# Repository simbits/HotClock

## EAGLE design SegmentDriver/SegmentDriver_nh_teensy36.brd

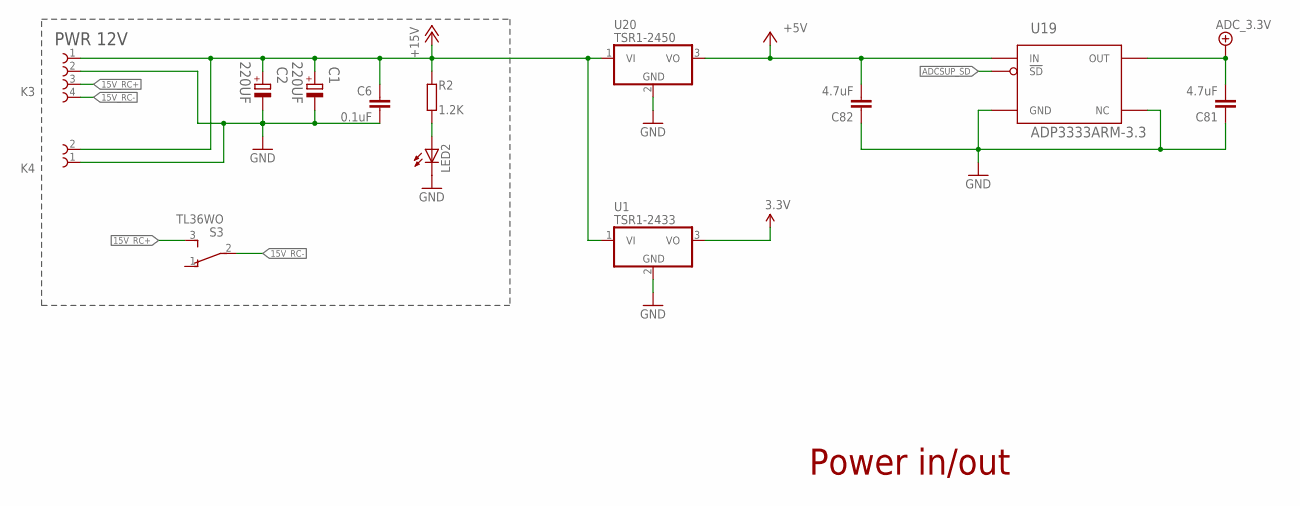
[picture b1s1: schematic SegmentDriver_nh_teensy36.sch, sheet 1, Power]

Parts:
C1, C2: 220UF; CAPAE830X1050N
C6: 0.1uF; C0603K
C81: 4.7uF; C0603K
C82: 4.7uF; C0805K
K3: 691322310004
K4: 691322310002
LED2: LEDCHIPLED_0603; CHIPLED_0603
R2: 1.2K; R0603
S3: TL36WO; TL3XWO
U1: TSR1-2433; TO220V_TR1; FARNELL_OC 1696320
U19: ADP3333ARM-3.3; MSOP-8
U20: TSR1-2450; TO220V_TR1; FARNELL_OC 1696320

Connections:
3.3V: U1.3 (VO); also elsewhere on the board
15V_RC+: K3.3, S3.3 (S)
15V_RC-: K3.4, S3.2
!ADCSUP_SD: U19.7 (!SD!); also elsewhere on the board
+5V: C82.2, U19.2 (IN), U20.3 (VO); also elsewhere on the board
+15V: C1.1, C2.1, C6.2, K3.1, K4.2, R2.2, U1.1 (VI), U20.1 (VI); also elsewhere on the board
ADC_3.3V: C81.2, U19.1 (OUT); also elsewhere on the board
GND: C1.2, C2.2, C6.1, C81.1, C82.1, K3.2, K4.1, LED2.C, U1.2 (GND), U19.3 (GND), U19.4 (NC), U19.5 (NC), U19.6 (NC), U19.8 (NC), U20.2 (GND); also elsewhere on the board
unnamed: LED2.A, R2.1

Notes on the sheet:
PWR 12V
Power in/out

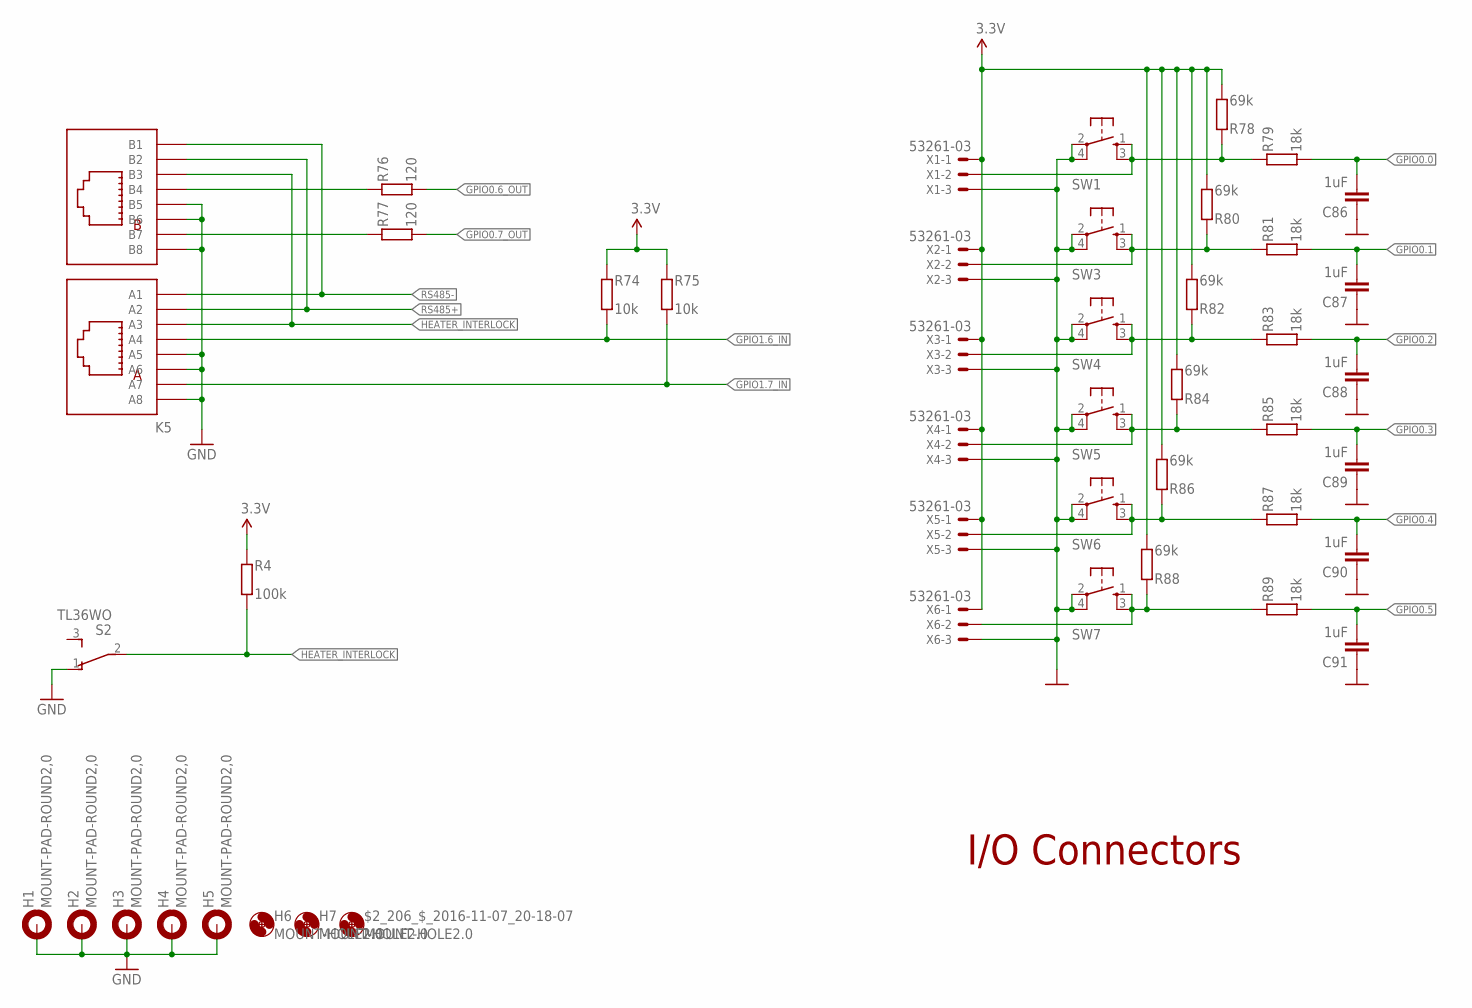
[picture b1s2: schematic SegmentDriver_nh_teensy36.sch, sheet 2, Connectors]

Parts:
$2_206_$_2016-11-07_20-18-07: MOUNT-HOLE2.0; 2,0
C86, C87, C88, C89, C90, C91: 1uF; C0603K
H1, H2, H3, H4, H5: MOUNT-PAD-ROUND2,0; 2,0-PAD
H6, H7: MOUNT-HOLE2.0; 2,0
K5: 615016149521
R4: 100k; R0603
R74, R75: 10k; R0603
R76, R77: 120; R0603
R78, R80, R82, R84, R86, R88: 69k; R0603
R79, R81, R83, R85, R87, R89: 18k; R0603
S2: TL36WO; TL3XWO
SW1, SW3, SW4, SW5, SW6, SW7: 434153017835_FIXED; 434153017835
X1, X2, X3, X4, X5, X6: 53261-03

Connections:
3.3V: R4.2, R74.2, R75.2, R78.1, R80.1, R82.1, R84.1, R86.1, R88.1, X1.1, X2.1, X3.1, X4.1, X5.1, X6.1; also elsewhere on the board
GND: C86.1, C87.1, C88.1, C89.1, C90.1, C91.1, H1.B2,2, H2.B2,2, H3.B2,2, H4.B2,2, H5.B2,2, K5.A5, K5.A6, K5.A8, K5.B5, K5.B6, K5.B8, S2.1 (O), SW1.2, SW1.4, SW3.2, SW3.4, SW4.2, SW4.4, SW5.2, SW5.4, SW6.2, SW6.4, SW7.2, SW7.4, X1.3, X2.3, X3.3, X4.3, X5.3, X6.3; also elsewhere on the board
GPIO0.0: C86.2, R79.1; also elsewhere on the board
GPIO0.1: C87.2, R81.1; also elsewhere on the board
GPIO0.2: C88.2, R83.1; also elsewhere on the board
GPIO0.3: C89.2, R85.1; also elsewhere on the board
GPIO0.4: C90.2, R87.1; also elsewhere on the board
GPIO0.5: C91.2, R89.1; also elsewhere on the board
GPIO0.6_OUT: R76.1; also elsewhere on the board
GPIO0.7_OUT: R77.1; also elsewhere on the board
GPIO1.6_IN: K5.A4, R74.1; also elsewhere on the board
GPIO1.7_IN: K5.A7, R75.1; also elsewhere on the board
GPIO6_OUT: K5.B4, R76.2
GPIO7_OUT: K5.B7, R77.2
HEATER_INTERLOCK: K5.A3, R4.1, S2.2; also elsewhere on the board
unnamed: R78.2, R79.2, SW1.1, SW1.3, X1.2
unnamed: R80.2, R81.2, SW3.1, SW3.3, X2.2
unnamed: R82.2, R83.2, SW4.1, SW4.3, X3.2
unnamed: R84.2, R85.2, SW5.1, SW5.3, X4.2
unnamed: R86.2, R87.2, SW6.1, SW6.3, X5.2
unnamed: R88.2, R89.2, SW7.1, SW7.3, X6.2
RS485+: K5.A2, K5.B2; also elsewhere on the board
RS485-: K5.A1, K5.B1; also elsewhere on the board

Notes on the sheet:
I/O Connectors

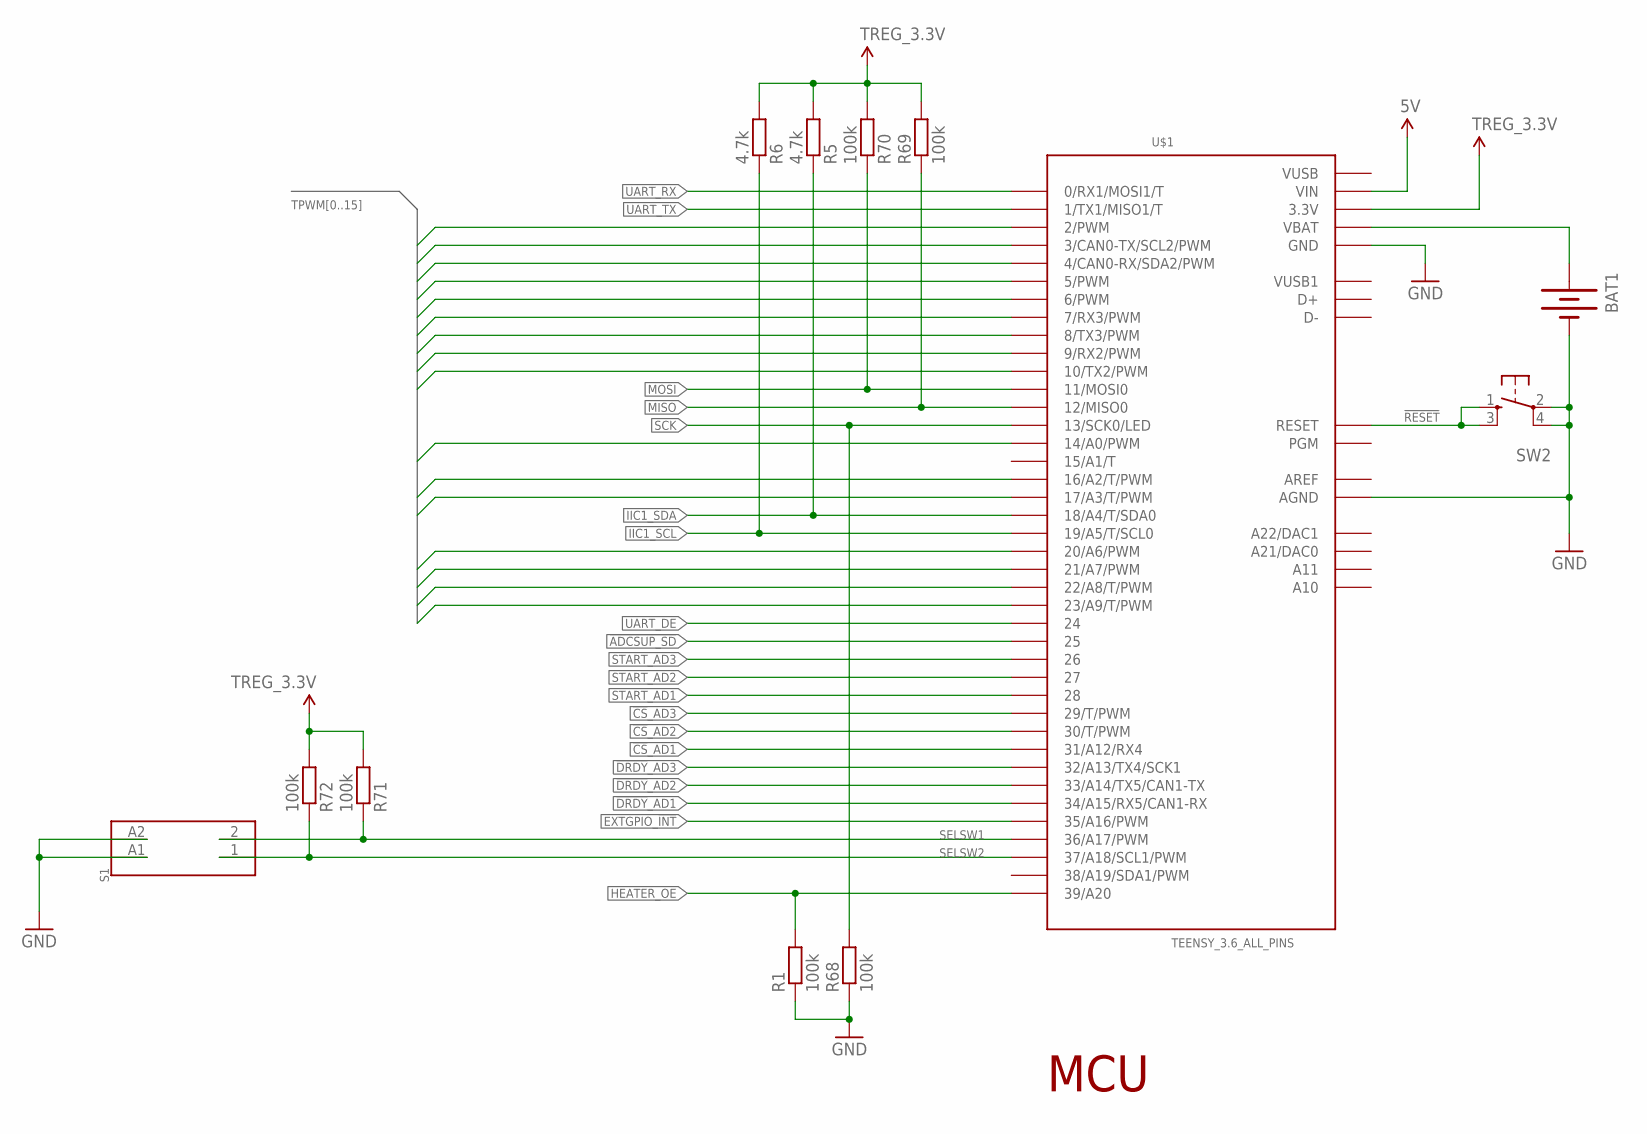
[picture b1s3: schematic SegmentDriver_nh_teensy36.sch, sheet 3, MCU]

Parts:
BAT1: BATTERY-79528211; 79528211; DIGIKEY BK-912-CT-ND
R1, R68, R69, R70, R71, R72: 100k; R0603
R5, R6: 4.7k; R0603
S1: 418127270902
SW2: 434153017835_FIXED; 434153017835
U$1: TEENSY_3.6_ALL_PINS

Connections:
5V: U$1.VIN
!ADCSUP_SD: U$1.25; also elsewhere on the board
!CS!_AD1: U$1.31/A12 (31/A12/RX4); also elsewhere on the board
!CS!_AD2: U$1.30 (30/T/PWM); also elsewhere on the board
!CS!_AD3: U$1.29 (29/T/PWM); also elsewhere on the board
!DRDY!_AD1: U$1.34/A15 (34/A15/RX5/CAN1-RX); also elsewhere on the board
!DRDY!_AD2: U$1.33/A14 (33/A14/TX5/CAN1-TX); also elsewhere on the board
!DRDY!_AD3: U$1.32/A13 (32/A13/TX4/SCK1); also elsewhere on the board
!RESET: SW2.1, SW2.3, U$1.RESET
AREF: U$1.AREF
EXTGPIO_!INT: U$1.35/A16 (35/A16/PWM); also elsewhere on the board
GND: BAT1.-, R1.1, R68.1, S1.A1, S1.A2, SW2.2, SW2.4, U$1.AGND, U$1.GND, U$1.GND1 (GND), U$1.GND3 (GND), U$1.GND4 (GND), U$1.GND6 (GND); also elsewhere on the board
HEATER_OE: R1.2, U$1.39/A20; also elsewhere on the board
IIC1_SCL: R6.1, U$1.19/A5 (19/A5/T/SCL0); also elsewhere on the board
IIC1_SDA: R5.1, U$1.18/A4 (18/A4/T/SDA0); also elsewhere on the board
MISO: R69.1, U$1.12 (12/MISO0); also elsewhere on the board
MOSI: R70.1, U$1.11 (11/MOSI0); also elsewhere on the board
unnamed: BAT1.+, U$1.VBAT
SCK: R68.2, U$1.13 (13/SCK0/LED); also elsewhere on the board
SELSW1: R71.1, S1.2, U$1.36/A17 (36/A17/PWM)
SELSW2: R72.1, S1.1, U$1.37/A18 (37/A18/SCL1/PWM)
START_AD1: U$1.28; also elsewhere on the board
START_AD2: U$1.27; also elsewhere on the board
START_AD3: U$1.26; also elsewhere on the board
TPWM0: U$1.2 (2/PWM)
TPWM1: U$1.3 (3/CAN0-TX/SCL2/PWM)
TPWM2: U$1.4 (4/CAN0-RX/SDA2/PWM)
TPWM3: U$1.5 (5/PWM)
TPWM4: U$1.6 (6/PWM)
TPWM5: U$1.7 (7/RX3/PWM)
TPWM6: U$1.8 (8/TX3/PWM)
TPWM7: U$1.9 (9/RX2/PWM)
TPWM8: U$1.10 (10/TX2/PWM)
TPWM9: U$1.14/A0 (14/A0/PWM)
TPWM10: U$1.16/A2 (16/A2/T/PWM)
TPWM11: U$1.17/A3 (17/A3/T/PWM)
TPWM12: U$1.20/A6 (20/A6/PWM)
TPWM13: U$1.21/A7 (21/A7/PWM)
TPWM14: U$1.22/A8 (22/A8/T/PWM)
TPWM15: U$1.23/A9 (23/A9/T/PWM)
TREG_3.3V: R5.2, R6.2, R69.2, R70.2, R71.2, R72.2, U$1.3.3V, U$1.3.3V3 (3.3V), U$1.3.3V4 (3.3V); also elsewhere on the board
UART_DE: U$1.24; also elsewhere on the board
UART_RX: U$1.0 (0/RX1/MOSI1/T); also elsewhere on the board
UART_TX: U$1.1 (1/TX1/MISO1/T); also elsewhere on the board
VUSB: U$1.VUSB
VUSB1: U$1.VUSB1

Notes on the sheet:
MCU

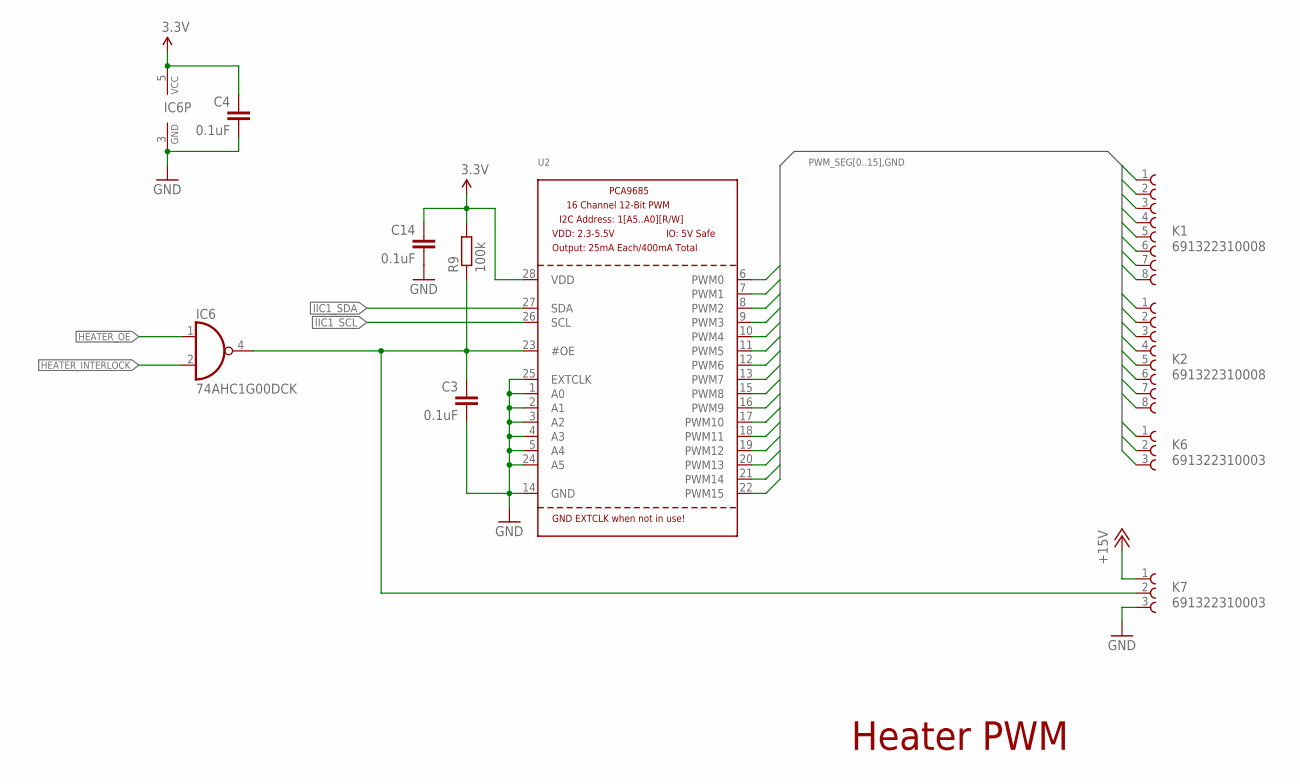
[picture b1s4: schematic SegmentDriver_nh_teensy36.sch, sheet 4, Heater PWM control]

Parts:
C3, C4, C14: 0.1uF; C0603K
IC6: 74AHC1G00DCK; SC70-5
K1, K2: 691322310008
K6, K7: 691322310003
R9: 100k; R0603
U2: PCA9685; TSSOP28

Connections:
3.3V: C4.1, C14.1, IC6.5 (VCC), R9.2, U2.28 (VDD); also elsewhere on the board
+15V: K7.1; also elsewhere on the board
GND: C3.2, C4.2, C14.2, IC6.3 (GND), K1.1, K2.1, K6.1, K7.3, U2.1 (A0), U2.2 (A1), U2.3 (A2), U2.4 (A3), U2.5 (A4), U2.14 (GND), U2.24 (A5), U2.25 (EXTCLK); also elsewhere on the board
HEATER_INTERLOCK: IC6.2 (I1); also elsewhere on the board
HEATER_OE: IC6.1 (I0); also elsewhere on the board
HEATER_PWR_EN: C3.1, IC6.4 (O), K7.2, R9.1, U2.23 (#OE)
IIC1_SCL: U2.26 (SCL); also elsewhere on the board
IIC1_SDA: U2.27 (SDA); also elsewhere on the board
PWM_SEG0: K1.2, U2.6 (PWM0)
PWM_SEG1: K1.3, U2.7 (PWM1)
PWM_SEG2: K1.4, U2.8 (PWM2)
PWM_SEG3: K1.5, U2.9 (PWM3)
PWM_SEG4: K1.6, U2.10 (PWM4)
PWM_SEG5: K1.7, U2.11 (PWM5)
PWM_SEG6: K1.8, U2.12 (PWM6)
PWM_SEG7: K2.2, U2.13 (PWM7)
PWM_SEG8: K2.3, U2.15 (PWM8)
PWM_SEG9: K2.4, U2.16 (PWM9)
PWM_SEG10: K2.5, U2.17 (PWM10)
PWM_SEG11: K2.6, U2.18 (PWM11)
PWM_SEG12: K2.7, U2.19 (PWM12)
PWM_SEG13: K2.8, U2.20 (PWM13)
PWM_SEG14: K6.2, U2.21 (PWM14)
PWM_SEG15: K6.3, U2.22 (PWM15)

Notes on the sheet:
Heater PWM

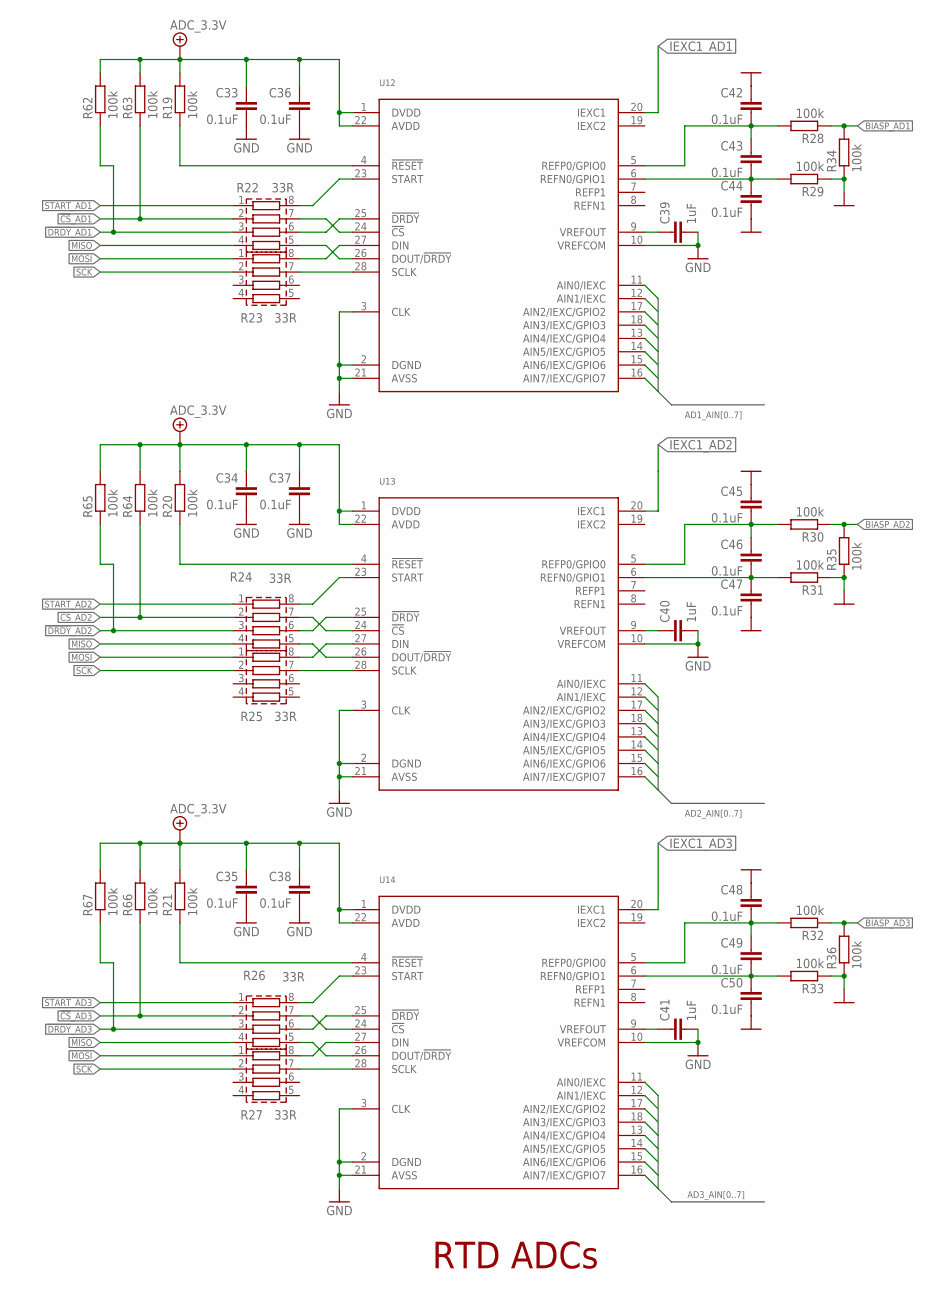
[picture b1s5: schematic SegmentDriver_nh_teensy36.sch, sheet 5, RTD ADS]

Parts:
C33, C34, C35, C36, C37, C38, C42, C43, C44, C45, C46, C47, C48, C49, C50: 0.1uF; C0603K
C39, C40, C41: 1uF; C0603K
R19, R20, R21, R28, R29, R30, R31, R32, R33, R34, R35, R36, R62, R63, R64, R65, R66, R67: 100k; R0603
R22, R23, R24, R25, R26, R27: 33R; RESCAV80P320X160X70-8N; MPN EXBV8V470JV
U12, U13, U14: ADS1X48IPW; TSSOP28

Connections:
9_AD1: C39.1, U12.9 (VREFOUT)
9_AD2: C40.1, U13.9 (VREFOUT)
9_AD3: C41.1, U14.9 (VREFOUT)
23_AD1: R22.8, U12.23 (START)
23_AD2: R24.8, U13.23 (START)
23_AD3: R26.8, U14.23 (START)
24_AD1: R22.7, U12.24 (!CS!)
24_AD2: R24.7, U13.24 (!CS!)
24_AD3: R26.7, U14.24 (!CS!)
25_AD1: R22.6, U12.25 (!DRDY!)
25_AD2: R24.6, U13.25 (!DRDY!)
25_AD3: R26.6, U14.25 (!DRDY!)
26_AD1: R22.5, U12.26 (DOUT/!DRDY!)
26_AD2: R24.5, U13.26 (DOUT/!DRDY!)
26_AD3: R26.5, U14.26 (DOUT/!DRDY!)
27_AD1: R23.8, U12.27 (DIN)
27_AD2: R25.8, U13.27 (DIN)
27_AD3: R27.8, U14.27 (DIN)
28_AD1: R23.7, U12.28 (SCLK)
28_AD2: R25.7, U13.28 (SCLK)
28_AD3: R27.7, U14.28 (SCLK)
!CS!_AD1: R22.2, R63.1; also elsewhere on the board
!CS!_AD2: R24.2, R64.1; also elsewhere on the board
!CS!_AD3: R26.2, R66.1; also elsewhere on the board
!DRDY!_AD1: R22.3, R62.1; also elsewhere on the board
!DRDY!_AD2: R24.3, R65.1; also elsewhere on the board
!DRDY!_AD3: R26.3, R67.1; also elsewhere on the board
!RESET!_AD1: R19.1, U12.4 (!RESET!)
!RESET!_AD2: R20.1, U13.4 (!RESET!)
!RESET!_AD3: R21.1, U14.4 (!RESET!)
AD1_AIN0: U12.11 (AIN0/IEXC); also elsewhere on the board
AD1_AIN1: U12.12 (AIN1/IEXC); also elsewhere on the board
AD1_AIN2: U12.17 (AIN2/IEXC/GPIO2); also elsewhere on the board
AD1_AIN3: U12.18 (AIN3/IEXC/GPIO3); also elsewhere on the board
AD1_AIN4: U12.13 (AIN4/IEXC/GPIO4); also elsewhere on the board
AD1_AIN5: U12.14 (AIN5/IEXC/GPIO5); also elsewhere on the board
AD1_AIN6: U12.15 (AIN6/IEXC/GPIO6); also elsewhere on the board
AD1_AIN7: U12.16 (AIN7/IEXC/GPIO7); also elsewhere on the board
AD2_AIN0: U13.11 (AIN0/IEXC); also elsewhere on the board
AD2_AIN1: U13.12 (AIN1/IEXC); also elsewhere on the board
AD2_AIN2: U13.17 (AIN2/IEXC/GPIO2); also elsewhere on the board
AD2_AIN3: U13.18 (AIN3/IEXC/GPIO3); also elsewhere on the board
AD2_AIN4: U13.13 (AIN4/IEXC/GPIO4); also elsewhere on the board
AD2_AIN5: U13.14 (AIN5/IEXC/GPIO5); also elsewhere on the board
AD2_AIN6: U13.15 (AIN6/IEXC/GPIO6); also elsewhere on the board
AD2_AIN7: U13.16 (AIN7/IEXC/GPIO7); also elsewhere on the board
AD3_AIN0: U14.11 (AIN0/IEXC); also elsewhere on the board
AD3_AIN1: U14.12 (AIN1/IEXC); also elsewhere on the board
AD3_AIN2: U14.17 (AIN2/IEXC/GPIO2); also elsewhere on the board
AD3_AIN3: U14.18 (AIN3/IEXC/GPIO3); also elsewhere on the board
AD3_AIN4: U14.13 (AIN4/IEXC/GPIO4); also elsewhere on the board
AD3_AIN5: U14.14 (AIN5/IEXC/GPIO5); also elsewhere on the board
AD3_AIN6: U14.15 (AIN6/IEXC/GPIO6); also elsewhere on the board
AD3_AIN7: U14.16 (AIN7/IEXC/GPIO7); also elsewhere on the board
ADC_3.3V: C33.1, C34.1, C35.1, C36.1, C37.1, C38.1, R19.2, R20.2, R21.2, R62.2, R63.2, R64.2, R65.2, R66.2, R67.2, U12.1 (DVDD), U12.22 (AVDD), U13.1 (DVDD), U13.22 (AVDD), U14.1 (DVDD), U14.22 (AVDD); also elsewhere on the board
BIASP_AD1: R28.1, R34.2; also elsewhere on the board
BIASP_AD2: R30.1, R35.2; also elsewhere on the board
BIASP_AD3: R32.1, R36.2; also elsewhere on the board
GND: C33.2, C34.2, C35.2, C36.2, C37.2, C38.2, C39.2, C40.2, C41.2, C42.1, C44.2, C45.1, C47.2, C48.1, C50.2, R29.1, R31.1, R33.1, R34.1, R35.1, R36.1, U12.2 (DGND), U12.3 (CLK), U12.10 (VREFCOM), U12.21 (AVSS), U13.2 (DGND), U13.3 (CLK), U13.10 (VREFCOM), U13.21 (AVSS), U14.2 (DGND), U14.3 (CLK), U14.10 (VREFCOM), U14.21 (AVSS); also elsewhere on the board
IEXC1_AD1: U12.20 (IEXC1); also elsewhere on the board
IEXC1_AD2: U13.20 (IEXC1); also elsewhere on the board
IEXC1_AD3: U14.20 (IEXC1); also elsewhere on the board
MISO: R22.4, R24.4, R26.4; also elsewhere on the board
MOSI: R23.1, R25.1, R27.1; also elsewhere on the board
REFN0_AD1: C43.2, C44.1, R29.2, U12.6 (REFN0/GPIO1)
REFN0_AD2: C46.2, C47.1, R31.2, U13.6 (REFN0/GPIO1)
REFN0_AD3: C49.2, C50.1, R33.2, U14.6 (REFN0/GPIO1)
REFP0_AD1: C42.2, C43.1, R28.2, U12.5 (REFP0/GPIO0)
REFP0_AD2: C45.2, C46.1, R30.2, U13.5 (REFP0/GPIO0)
REFP0_AD3: C48.2, C49.1, R32.2, U14.5 (REFP0/GPIO0)
SCK: R23.2, R25.2, R27.2; also elsewhere on the board
START_AD1: R22.1; also elsewhere on the board
START_AD2: R24.1; also elsewhere on the board
START_AD3: R26.1; also elsewhere on the board

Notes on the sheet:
RTD ADCs

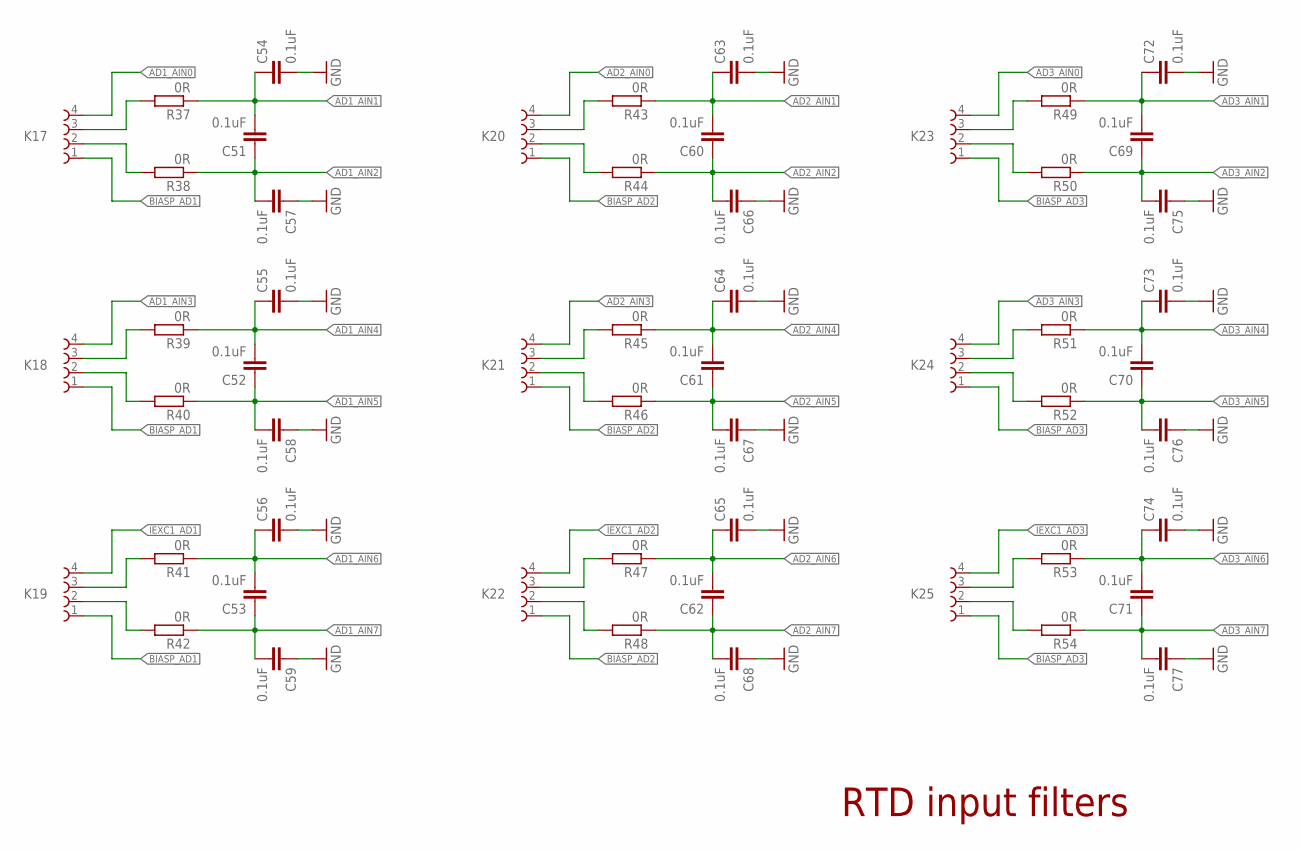
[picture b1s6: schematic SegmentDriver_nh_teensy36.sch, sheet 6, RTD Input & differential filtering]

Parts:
C51, C52, C53, C54, C55, C56, C57, C58, C59, C60, C61, C62, C63, C64, C65, C66, C67, C68, C69, C70, C71, C72, C73, C74, C75, C76, C77: 0.1uF; C0603K
K17, K18, K19, K20, K21, K22, K23, K24, K25: 691210910004
R37, R38, R39, R40, R41, R42, R43, R44, R45, R46, R47, R48, R49, R50, R51, R52, R53, R54: 0R; R0603

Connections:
AD1_AIN0: K17.4; also elsewhere on the board
AD1_AIN1: C51.2, C54.1, R37.1; also elsewhere on the board
AD1_AIN2: C51.1, C57.2, R38.1; also elsewhere on the board
AD1_AIN3: K18.4; also elsewhere on the board
AD1_AIN4: C52.2, C55.1, R39.1; also elsewhere on the board
AD1_AIN5: C52.1, C58.2, R40.1; also elsewhere on the board
AD1_AIN6: C53.2, C56.1, R41.1; also elsewhere on the board
AD1_AIN7: C53.1, C59.2, R42.1; also elsewhere on the board
AD2_AIN0: K20.4; also elsewhere on the board
AD2_AIN1: C60.2, C63.1, R43.1; also elsewhere on the board
AD2_AIN2: C60.1, C66.2, R44.1; also elsewhere on the board
AD2_AIN3: K21.4; also elsewhere on the board
AD2_AIN4: C61.2, C64.1, R45.1; also elsewhere on the board
AD2_AIN5: C61.1, C67.2, R46.1; also elsewhere on the board
AD2_AIN6: C62.2, C65.1, R47.1; also elsewhere on the board
AD2_AIN7: C62.1, C68.2, R48.1; also elsewhere on the board
AD3_AIN0: K23.4; also elsewhere on the board
AD3_AIN1: C69.2, C72.1, R49.1; also elsewhere on the board
AD3_AIN2: C69.1, C75.2, R50.1; also elsewhere on the board
AD3_AIN3: K24.4; also elsewhere on the board
AD3_AIN4: C70.2, C73.1, R51.1; also elsewhere on the board
AD3_AIN5: C70.1, C76.2, R52.1; also elsewhere on the board
AD3_AIN6: C71.2, C74.1, R53.1; also elsewhere on the board
AD3_AIN7: C71.1, C77.2, R54.1; also elsewhere on the board
BIASP_AD1: K17.1, K18.1, K19.1; also elsewhere on the board
BIASP_AD2: K20.1, K21.1, K22.1; also elsewhere on the board
BIASP_AD3: K23.1, K24.1, K25.1; also elsewhere on the board
GND: C54.2, C55.2, C56.2, C57.1, C58.1, C59.1, C63.2, C64.2, C65.2, C66.1, C67.1, C68.1, C72.2, C73.2, C74.2, C75.1, C76.1, C77.1; also elsewhere on the board
IEXC1_AD1: K19.4; also elsewhere on the board
IEXC1_AD2: K22.4; also elsewhere on the board
IEXC1_AD3: K25.4; also elsewhere on the board
unnamed: K18.3, R39.2
unnamed: K18.2, R40.2
unnamed: K17.3, R37.2
unnamed: K17.2, R38.2
unnamed: K19.3, R41.2
unnamed: K19.2, R42.2
unnamed: K20.3, R43.2
unnamed: K20.2, R44.2
unnamed: K21.3, R45.2
unnamed: K21.2, R46.2
unnamed: K22.3, R47.2
unnamed: K22.2, R48.2
unnamed: K23.3, R49.2
unnamed: K23.2, R50.2
unnamed: K24.3, R51.2
unnamed: K24.2, R52.2
unnamed: K25.3, R53.2
unnamed: K25.2, R54.2

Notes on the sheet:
RTD input filters

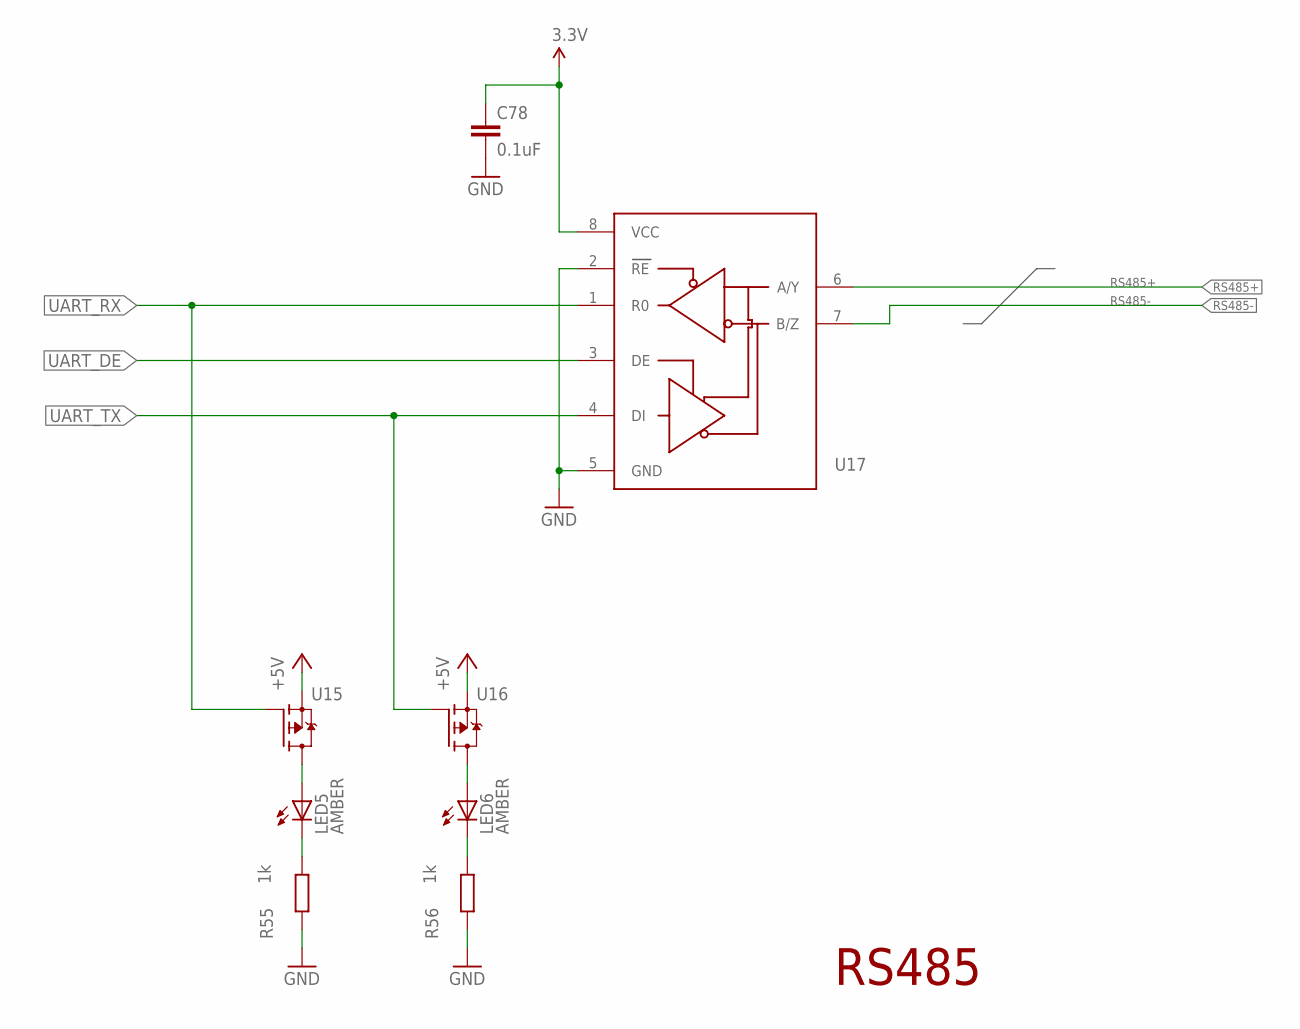
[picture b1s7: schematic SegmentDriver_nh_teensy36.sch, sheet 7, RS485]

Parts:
C78: 0.1uF; C0603K
LED5, LED6: AMBER; CHIPLED_0603
R55, R56: 1k; R0603
U15, U16: DMP2215L-7; SOT95P240X110-3N
U17: ISL83078E; SOIC08

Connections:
3.3V: C78.1, U17.8 (VCC); also elsewhere on the board
+5V: U15.2 (S), U16.2 (S); also elsewhere on the board
GND: C78.2, R55.1, R56.1, U17.2 (RE), U17.5 (GND); also elsewhere on the board
unnamed: LED5.C, R55.2
unnamed: LED6.C, R56.2
unnamed: LED5.A, U15.3 (D)
unnamed: LED6.A, U16.3 (D)
RS485+: U17.6 (A/Y); also elsewhere on the board
RS485-: U17.7 (B/Z); also elsewhere on the board
UART_DE: U17.3 (DE); also elsewhere on the board
UART_RX: U15.1 (G), U17.1 (R0); also elsewhere on the board
UART_TX: U16.1 (G), U17.4 (DI); also elsewhere on the board

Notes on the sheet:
RS485

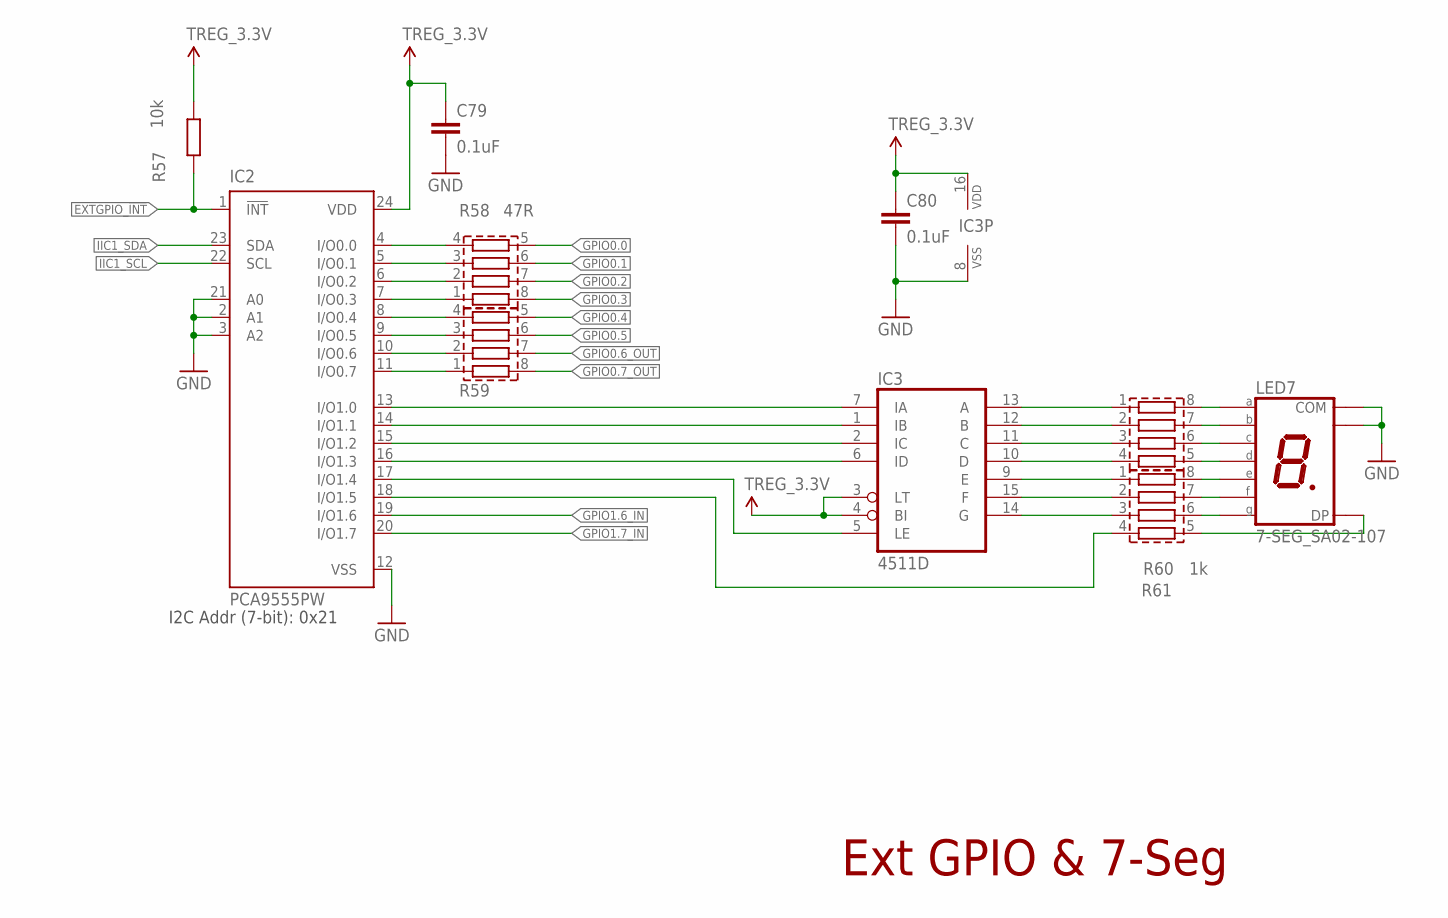
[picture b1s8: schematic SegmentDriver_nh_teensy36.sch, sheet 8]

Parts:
C79, C80: 0.1uF; C0603K
IC2: PCA9555PW; TSSOP24
IC3: 4511D; SO16
LED7: 7-SEG_SA02-107; SA02107
R57: 10k; R0603
R58, R59: 47R; RESCAV80P320X160X70-8N; MPN EXBV8V470JV
R60: 47R; RESCAV80P320X160X70-8N; MPN EXBV8V102JV
R61: 1k; RESCAV80P320X160X70-8N; MPN EXBV8V102JV

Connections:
EXTGPIO_!INT: IC2.1 (!INT), R57.1; also elsewhere on the board
GND: C79.2, C80.2, IC2.2 (A1), IC2.3 (A2), IC2.12 (VSS), IC2.21 (A0), IC3.8 (VSS), LED7.COM@3 (COM), LED7.COM@8 (COM); also elsewhere on the board
GPIO0.0: R58.5; also elsewhere on the board
GPIO0.1: R58.6; also elsewhere on the board
GPIO0.2: R58.7; also elsewhere on the board
GPIO0.3: R58.8; also elsewhere on the board
GPIO0.4: R59.5; also elsewhere on the board
GPIO0.5: R59.6; also elsewhere on the board
GPIO0.6_OUT: R59.7; also elsewhere on the board
GPIO0.7_OUT: R59.8; also elsewhere on the board
GPIO1.6_IN: IC2.19 (I/O1.6); also elsewhere on the board
GPIO1.7_IN: IC2.20 (I/O1.7); also elsewhere on the board
IIC1_SCL: IC2.22 (SCL); also elsewhere on the board
IIC1_SDA: IC2.23 (SDA); also elsewhere on the board
unnamed: IC2.4 (I/O0.0), R58.4
unnamed: IC2.5 (I/O0.1), R58.3
unnamed: IC2.6 (I/O0.2), R58.2
unnamed: IC2.7 (I/O0.3), R58.1
unnamed: IC2.8 (I/O0.4), R59.4
unnamed: IC2.9 (I/O0.5), R59.3
unnamed: IC2.10 (I/O0.6), R59.2
unnamed: IC2.11 (I/O0.7), R59.1
unnamed: IC2.13 (I/O1.0), IC3.7 (IA)
unnamed: IC3.13 (A), R60.1
unnamed: IC3.12 (B), R60.2
unnamed: IC3.11 (C), R60.3
unnamed: IC3.10 (D), R60.4
unnamed: IC3.9 (E), R61.1
unnamed: IC3.15 (F), R61.2
unnamed: IC3.14 (G), R61.3
unnamed: LED7.A@7 (A), R60.8
unnamed: LED7.B@6 (B), R60.7
unnamed: LED7.C@4 (C), R60.6
unnamed: LED7.D@2 (D), R60.5
unnamed: LED7.E@1 (E), R61.8
unnamed: LED7.F@9 (F), R61.7
unnamed: LED7.G@10 (G), R61.6
unnamed: LED7.DP@5 (DP), R61.5
unnamed: IC2.14 (I/O1.1), IC3.1 (IB)
unnamed: IC2.15 (I/O1.2), IC3.2 (IC)
unnamed: IC2.16 (I/O1.3), IC3.6 (ID)
unnamed: IC2.17 (I/O1.4), IC3.5 (LE)
unnamed: IC2.18 (I/O1.5), R61.4
TREG_3.3V: C79.1, C80.1, IC2.24 (VDD), IC3.3 (LT), IC3.4 (BI), IC3.16 (VDD), R57.2; also elsewhere on the board

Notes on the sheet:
I2C Addr (7-bit): 0x21
Ext GPIO & 7-Seg

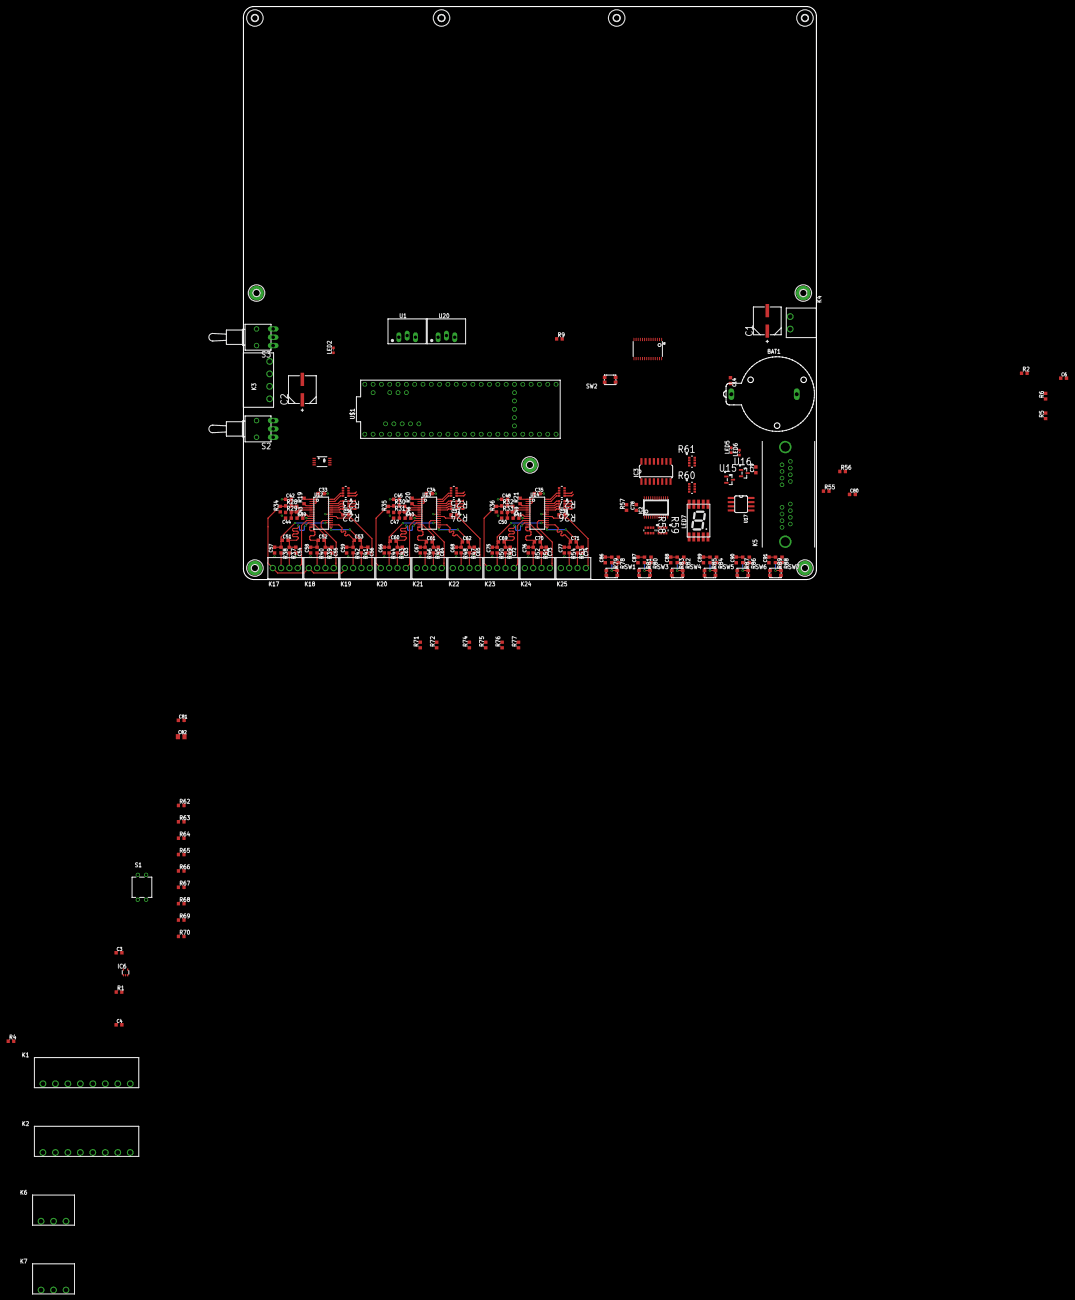
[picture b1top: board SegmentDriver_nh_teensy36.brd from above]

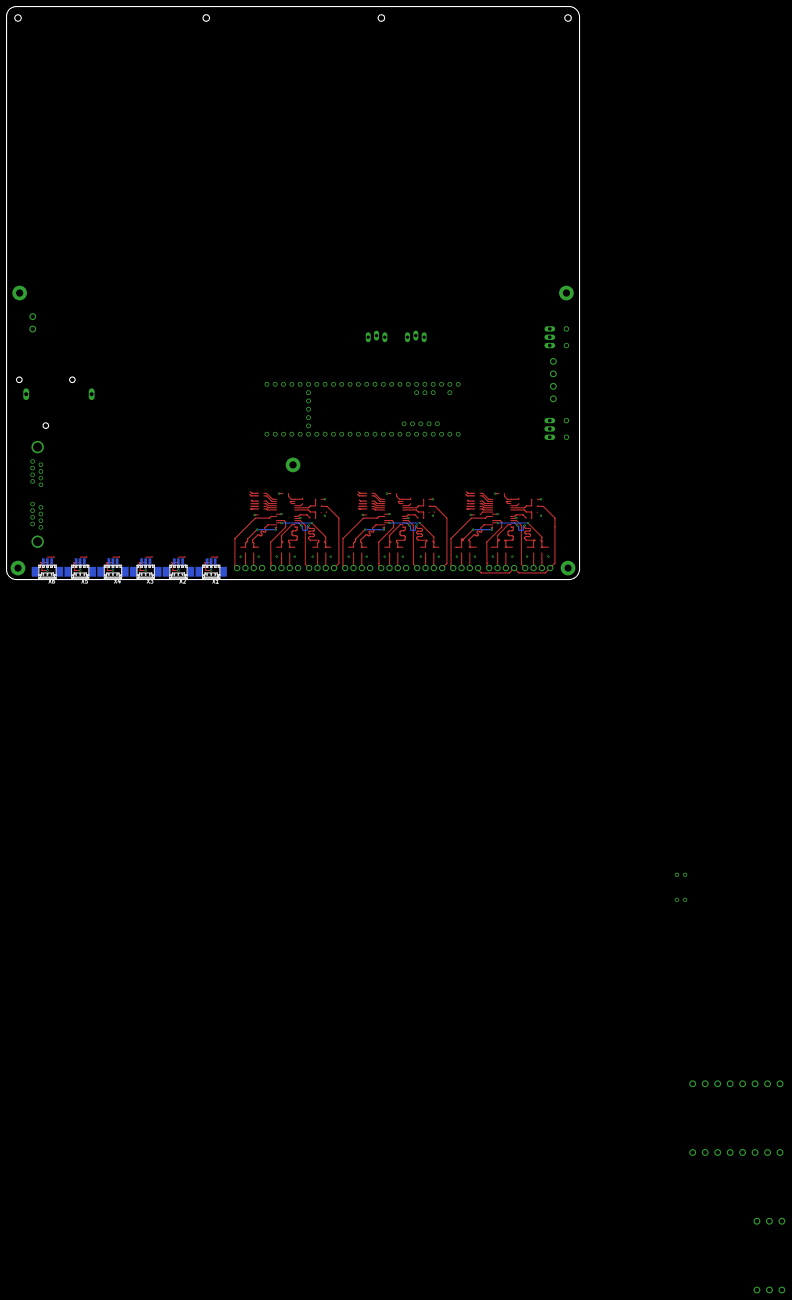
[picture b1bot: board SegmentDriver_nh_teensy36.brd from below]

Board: 2 copper layers, 175.0 x 175.0 mm, 198 parts (6 on the bottom side), 182 nets.

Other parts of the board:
H8: MOUNT-HOLE2.0; 2,0

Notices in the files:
parts and their libraries:
Wurth_Elektronik_Electromechanic_Termina: Copyright: Würth Elektronik
